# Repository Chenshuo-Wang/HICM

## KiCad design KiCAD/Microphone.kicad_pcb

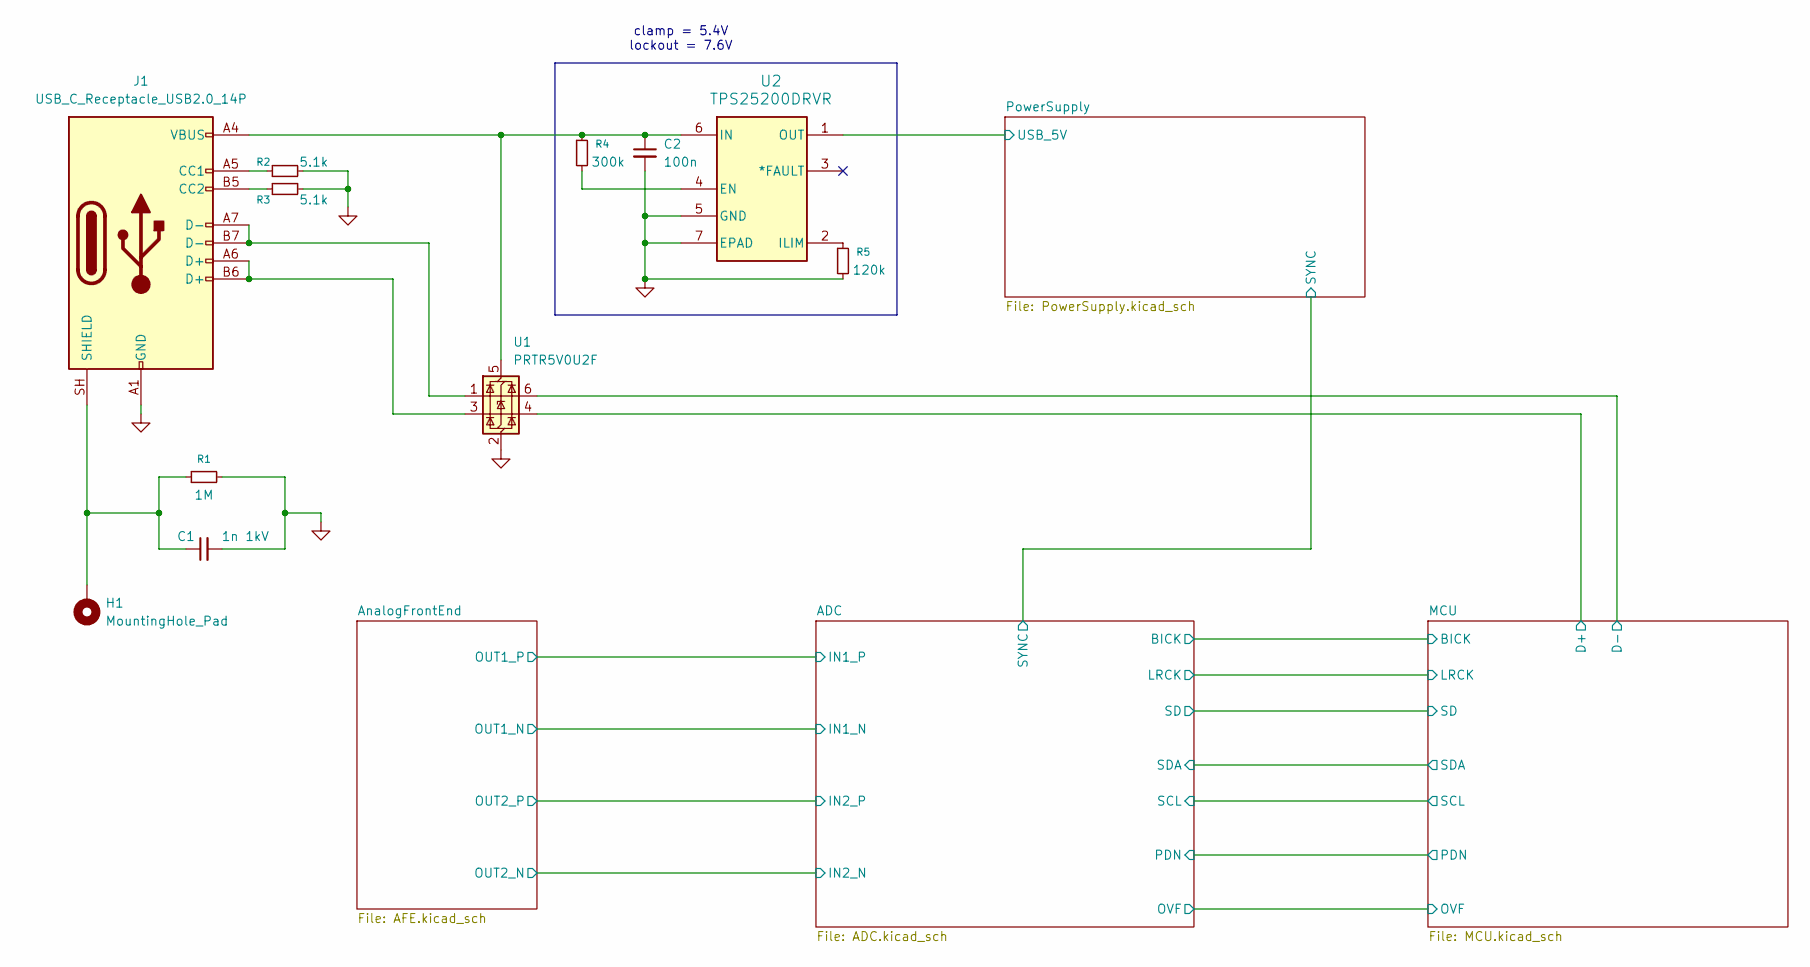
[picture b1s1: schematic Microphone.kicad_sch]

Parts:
C1: 1n 1kV; C_1206_3216Metric
C2: 100n; C_0402_1005Metric
H1: MountingHole_Pad; MountingHole_2.2mm_M2_Pad_Via
J1: USB_C_Receptacle_USB2.0_14P; USB_C_Receptacle_GCT_USB4110
R1: 1M; R_0805_2012Metric
R2, R3: 5.1k; R_0402_1005Metric
R4: 300k; R_0402_1005Metric
R5: 120k; R_0402_1005Metric
U1: PRTR5V0U2F; SOT-886
U2: TPS25200DRVR; DRV6_1X1P6_TEX

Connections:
/MCU/D+: U1.4 (I/O2); also elsewhere on the board
/MCU/D-: U1.6 (I/O1); also elsewhere on the board
/PowerSupply/USB_5V: U2.1 (OUT); also elsewhere on the board
GND: C1.2, C2.2, J1.A1 (GND), J1.A12 (GND), J1.B1 (GND), J1.B12 (GND), R1.2, R2.2, R3.1, R5.2, U1.2 (GND), U2.5 (GND), U2.7 (EPAD); also elsewhere on the board
unnamed: J1.A5 (CC1), R2.1
unnamed: J1.B5 (CC2), R3.2
unnamed: J1.A6 (D+), J1.B6 (D+), U1.3 (I/O2)
unnamed: J1.A7 (D-), J1.B7 (D-), U1.1 (I/O1)
unnamed: C1.1, H1.1 (1_1), J1.SH (SHIELD), R1.1
unnamed: C2.1, J1.A4 (VBUS), J1.A9 (VBUS), J1.B4 (VBUS), J1.B9 (VBUS), R4.1, U1.5 (VBUS), U2.6 (IN)
unnamed: R4.2, U2.4 (EN)
unnamed: R5.1, U2.2 (ILIM)

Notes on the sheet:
clamp = 5.4V lockout = 7.6V

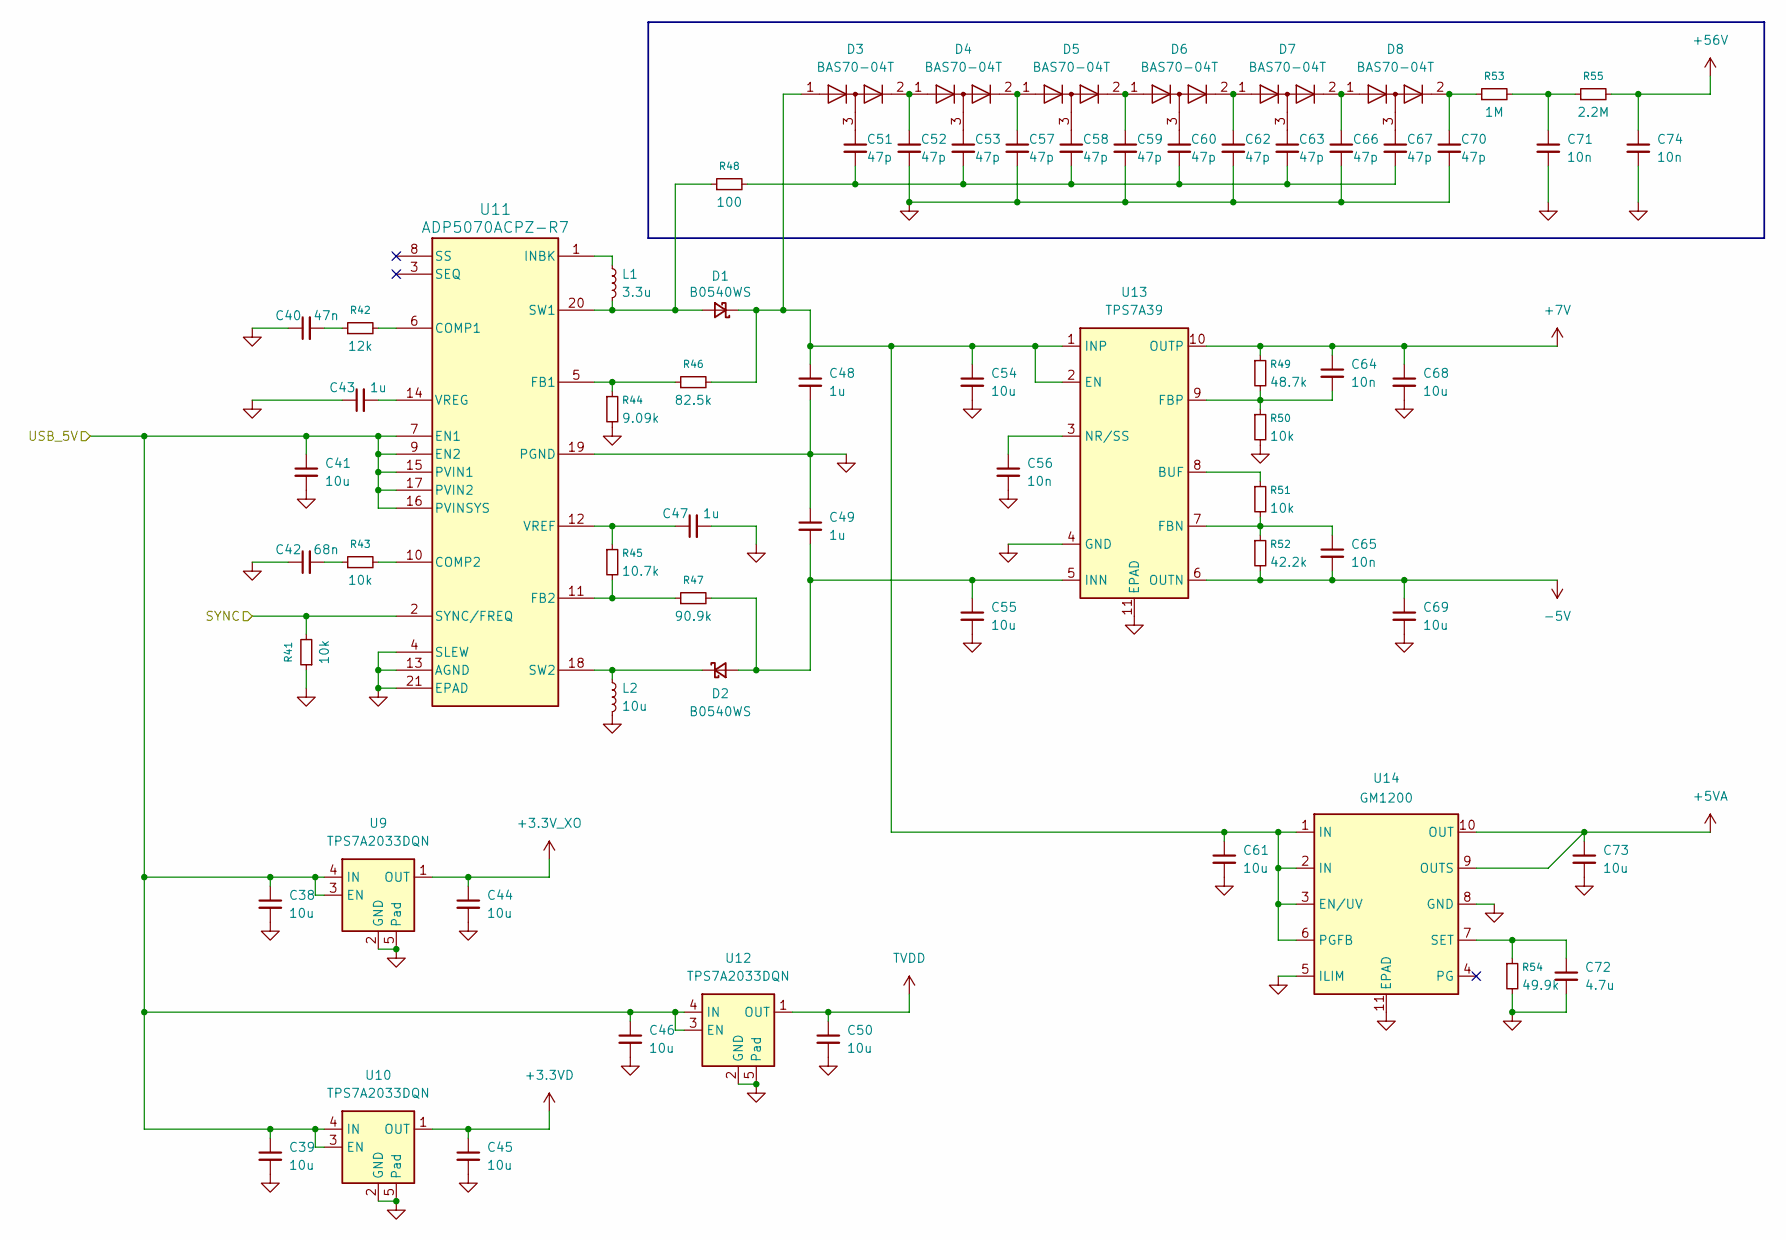
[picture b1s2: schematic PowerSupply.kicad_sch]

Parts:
C38, C39, C44, C45, C46, C50, C54, C55, C61, C68, C69, C73: 10u; C_0603_1608Metric
C40: 47n; C_0402_1005Metric
C41: 10u; C_0805_2012Metric
C42: 68n; C_0402_1005Metric
C43, C47: 1u; C_0402_1005Metric
C48, C49: 1u; C_0603_1608Metric
C51, C52, C53, C57, C58, C59, C60, C62, C63, C66, C67, C70: 47p; C_0603_1608Metric
C56, C64, C65: 10n; C_0402_1005Metric
C71, C74: 10n; C_0603_1608Metric
C72: 4.7u; C_0603_1608Metric
D1, D2: B0540WS; D_SOD-323
D3, D4, D5, D6, D7, D8: BAS70-04T; SOT-523
L1: 3.3u; IND_SPM4020_TDK
L2: 10u; IND_SPM4020_TDK
R41, R43, R50, R51: 10k; R_0402_1005Metric
R42: 12k; R_0402_1005Metric
R44: 9.09k; R_0402_1005Metric
R45: 10.7k; R_0402_1005Metric
R46: 82.5k; R_0402_1005Metric
R47: 90.9k; R_0402_1005Metric
R48: 100; R_0805_2012Metric
R49: 48.7k; R_0402_1005Metric
R52: 42.2k; R_0402_1005Metric
R53: 1M; R_0805_2012Metric
R54: 49.9k; R_0402_1005Metric
R55: 2.2M; R_0805_2012Metric
U9, U10, U12: TPS7A2033DQN; Texas_X2SON-4_1x1mm_P0.65mm
U11: ADP5070ACPZ-R7; QFN-20-1EP_4x4mm_P0.5mm_EP2.6x2.6mm_ThermalVias
U13: TPS7A39; Texas_S-PVSON-N10_ThermalVias
U14: GM1200; DFN-10-1EP_3x3mm_P0.5mm_EP1.65x2.38mm_ThermalVias

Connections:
+3.3VD: C45.1, U10.1 (OUT); also elsewhere on the board
+3.3V_XO: C44.1, U9.1 (OUT); also elsewhere on the board
+5VA: C73.1, U14.9 (OUTS), U14.10 (OUT); also elsewhere on the board
+7V: C64.1, C68.1, R49.1, U13.10 (OUTP); also elsewhere on the board
+56V: C74.1, R55.2; also elsewhere on the board
-5V: C65.2, C69.1, R52.2, U13.6 (OUTN); also elsewhere on the board
/ADC/SYNC: R41.2, U11.2 (SYNC/FREQ); also elsewhere on the board
/PowerSupply/USB_5V: C38.1, C39.1, C41.1, C46.1, U9.3 (EN), U9.4 (IN), U10.3 (EN), U10.4 (IN), U11.7 (EN1), U11.9 (EN2), U11.15 (PVIN1), U11.16 (PVINSYS), U11.17 (PVIN2), U12.3 (EN), U12.4 (IN); also elsewhere on the board
GND: C38.2, C39.2, C40.1, C41.2, C42.1, C43.1, C44.2, C45.2, C46.2, C47.2, C48.2, C49.1, C50.2, C52.2, C54.2, C55.2, C56.2, C57.2, C59.2, C61.2, C62.2, C66.2, C68.2, C69.2, C70.2, C71.2, C72.2, C73.2, C74.2, L2.2, R41.1, R44.2, R50.2, R54.2, U9.2 (GND), U9.5 (Pad), U10.2 (GND), U10.5 (Pad), U11.4 (SLEW), U11.13 (AGND), U11.19 (PGND), U11.21 (EPAD), U12.2 (GND), U12.5 (Pad), U13.4 (GND), U13.11 (EPAD), U14.5 (ILIM), U14.8 (GND), U14.11 (EPAD); also elsewhere on the board
unnamed: C40.2, R42.1
unnamed: C42.2, R43.1
unnamed: C51.1, D3.3 (K)
unnamed: C51.2, C53.2, C58.2, C60.2, C63.2, C67.2, R48.2
unnamed: C53.1, D4.3 (K)
unnamed: C58.1, D5.3 (K)
unnamed: C60.1, D6.3 (K)
unnamed: C63.1, D7.3 (K)
unnamed: C67.1, D8.3 (K)
unnamed: C71.1, R53.2, R55.1
unnamed: D1.2 (A), L1.2, R48.1, U11.20 (SW1)
unnamed: C48.1, C54.1, C61.1, D1.1 (K), D3.1 (K), R46.2, U13.1 (INP), U13.2 (EN), U14.1 (IN), U14.2 (IN), U14.3 (EN/UV), U14.6 (PGFB)
unnamed: C49.2, C55.1, D2.2 (A), R47.2, U13.5 (INN)
unnamed: D2.1 (K), L2.1, U11.18 (SW2)
unnamed: C52.1, D3.2 (A), D4.1 (K)
unnamed: C57.1, D4.2 (A), D5.1 (K)
unnamed: C59.1, D5.2 (A), D6.1 (K)
unnamed: C62.1, D6.2 (A), D7.1 (K)
unnamed: C66.1, D7.2 (A), D8.1 (K)
unnamed: C70.1, D8.2 (A), R53.1
unnamed: R42.2, U11.6 (COMP1)
unnamed: R43.2, U11.10 (COMP2)
unnamed: R44.1, R46.1, U11.5 (FB1)
unnamed: R45.2, R47.1, U11.11 (FB2)
unnamed: L1.1, U11.1 (INBK)
unnamed: C47.1, R45.1, U11.12 (VREF)
unnamed: C43.2, U11.14 (VREG)
unnamed: R51.1, U13.8 (BUF)
unnamed: C65.1, R51.2, R52.1, U13.7 (FBN)
unnamed: C64.2, R49.2, R50.1, U13.9 (FBP)
unnamed: C56.1, U13.3 (NR/SS)
unnamed: C72.1, R54.1, U14.7 (SET)
TVDD: C50.1, U12.1 (OUT); also elsewhere on the board

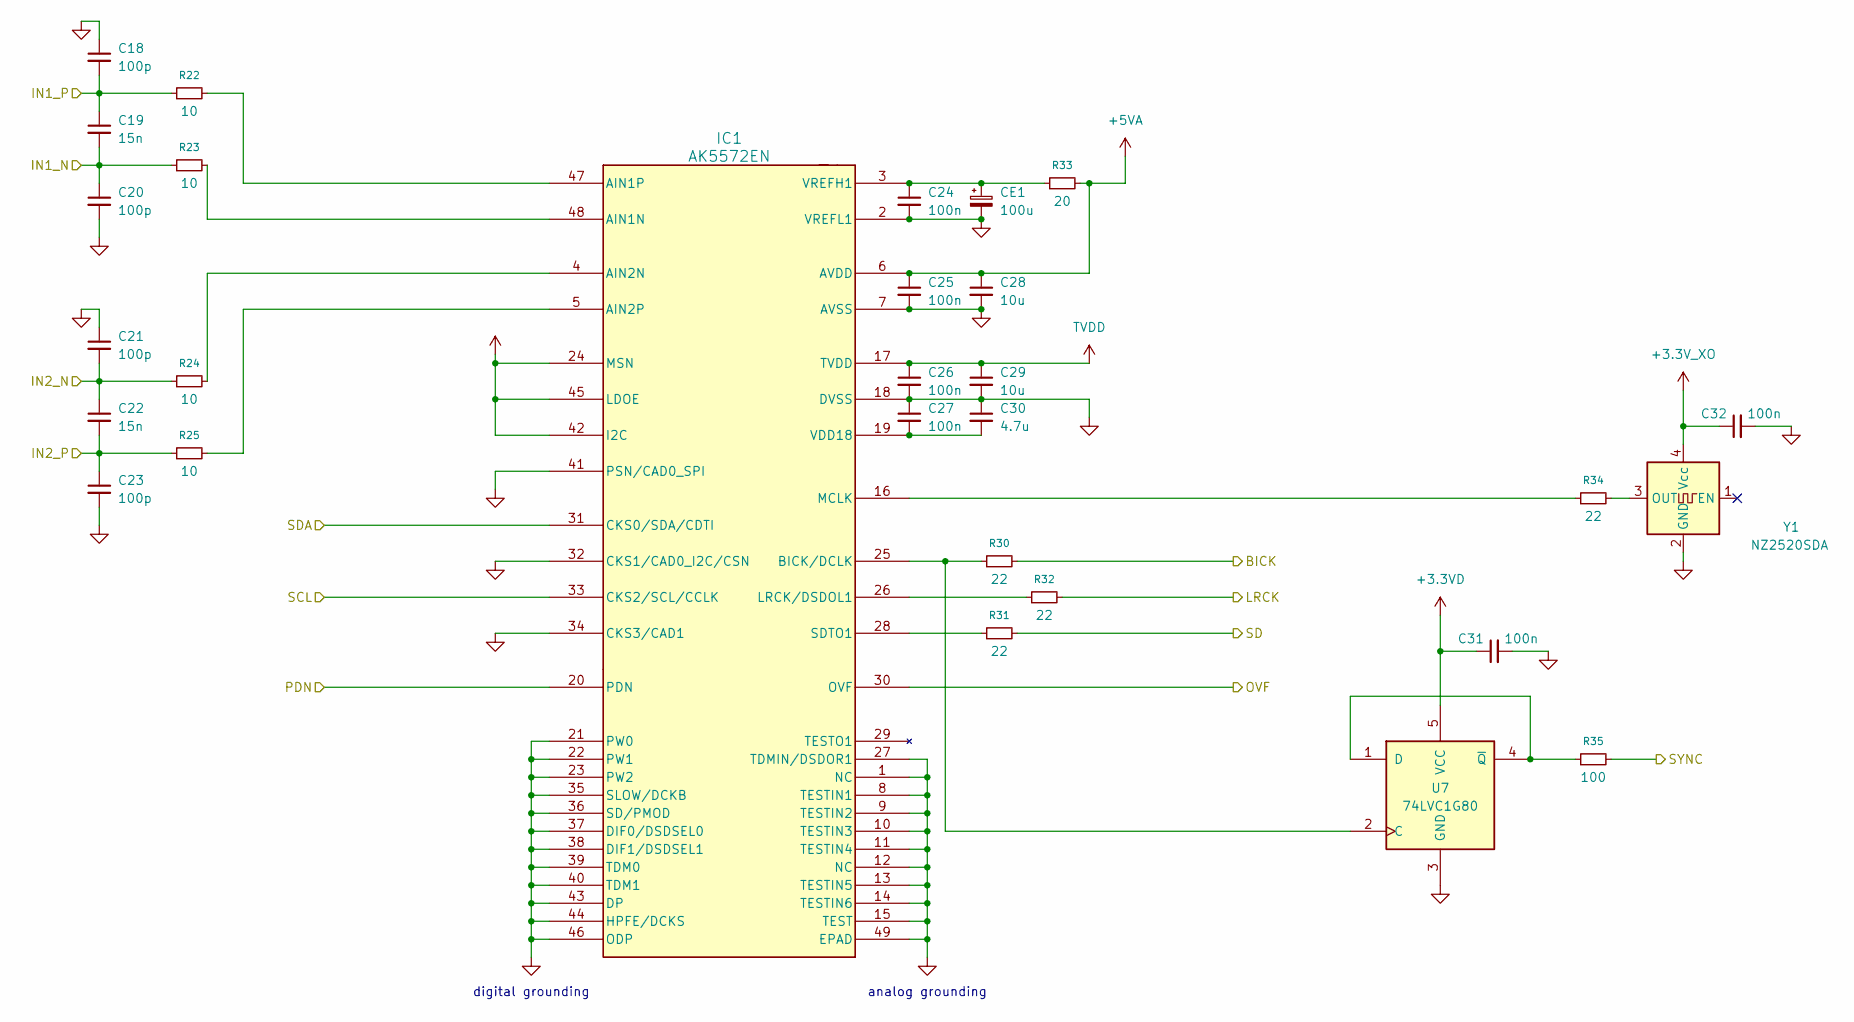
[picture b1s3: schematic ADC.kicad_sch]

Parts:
C18, C20, C21, C23: 100p; C_0402_1005Metric
C19, C22: 15n; C_0402_1005Metric
C24, C25, C26, C27, C31, C32: 100n; C_0402_1005Metric
C28, C29: 10u; C_0603_1608Metric
C30: 4.7u; C_0603_1608Metric
CE1: 100u; CP_EIA-3528-21_Kemet-B
IC1: AK5572EN; QFN-48-1EP_7x7mm_P0.5mm_EP5.1x5.1mm_ThermalVias
R22, R23, R24, R25: 10; R_0402_1005Metric
R30, R31, R32, R34: 22; R_0402_1005Metric
R33: 20; R_0805_2012Metric
R35: 100; R_0402_1005Metric
U7: 74LVC1G80; SOT-353_SC-70-5
Y1: NZ2520SDA; Oscillator_SMD_SeikoEpson_SG210-4Pin_2.5x2.0mm

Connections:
+3.3VD: C31.1, U7.5 (VCC); also elsewhere on the board
+3.3V_XO: C32.1, Y1.4 (Vcc); also elsewhere on the board
+5VA: C25.1, C28.1, IC1.6 (AVDD), R33.2; also elsewhere on the board
/ADC/BICK: R30.2; also elsewhere on the board
/ADC/IN1_N: C19.2, C20.1, R23.1; also elsewhere on the board
/ADC/IN1_P: C18.2, C19.1, R22.1; also elsewhere on the board
/ADC/IN2_N: C21.2, C22.1, R24.1; also elsewhere on the board
/ADC/IN2_P: C22.2, C23.1, R25.1; also elsewhere on the board
/ADC/LRCK: R32.2; also elsewhere on the board
/ADC/OVF: IC1.30 (OVF); also elsewhere on the board
/ADC/PDN: IC1.20 (PDN); also elsewhere on the board
/ADC/SCL: IC1.33 (CKS2/SCL/CCLK); also elsewhere on the board
/ADC/SD: R31.2; also elsewhere on the board
/ADC/SDA: IC1.31 (CKS0/SDA/CDTI); also elsewhere on the board
/ADC/SYNC: R35.2; also elsewhere on the board
GND: C18.1, C20.2, C21.1, C23.2, C24.2, C25.2, C26.2, C27.1, C28.2, C29.2, C30.1, C31.2, C32.2, CE1.2, IC1.1 (NC), IC1.2 (VREFL1), IC1.7 (AVSS), IC1.8 (TESTIN1), IC1.9 (TESTIN2), IC1.10 (TESTIN3), IC1.11 (TESTIN4), IC1.12 (NC), IC1.13 (TESTIN5), IC1.14 (TESTIN6), IC1.15 (TEST), IC1.18 (DVSS), IC1.21 (PW0), IC1.22 (PW1), IC1.23 (PW2), IC1.27 (TDMIN/DSDOR1), IC1.32 (CKS1/CAD0_I2C/CSN), IC1.34 (CKS3/CAD1), IC1.35 (SLOW/DCKB), IC1.36 (SD/PMOD), IC1.37 (DIF0/DSDSEL0), IC1.38 (DIF1/DSDSEL1), IC1.39 (TDM0), IC1.40 (TDM1), IC1.41 (PSN/CAD0_SPI), IC1.43 (DP), IC1.44 (HPFE/DCKS), IC1.46 (ODP), IC1.49 (EPAD), U7.3 (GND), Y1.2 (GND); also elsewhere on the board
unnamed: IC1.48 (AIN1N), R23.2
unnamed: IC1.47 (AIN1P), R22.2
unnamed: IC1.4 (AIN2N), R24.2
unnamed: IC1.5 (AIN2P), R25.2
unnamed: IC1.25 (BICK/DCLK), R30.1, U7.2 (C)
unnamed: IC1.26 (LRCK/DSDOL1), R32.1
unnamed: IC1.16 (MCLK), R34.1
unnamed: IC1.28 (SDTO1), R31.1
unnamed: C27.2, C30.2, IC1.19 (VDD18)
unnamed: C24.1, CE1.1, IC1.3 (VREFH1), R33.1
unnamed: R35.1, U7.1 (D), U7.4 (~Q)
unnamed: R34.2, Y1.3 (OUT)
TVDD: C26.1, C29.1, IC1.17 (TVDD), IC1.24 (MSN), IC1.42 (I2C), IC1.45 (LDOE); also elsewhere on the board

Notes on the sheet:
analog grounding
digital grounding

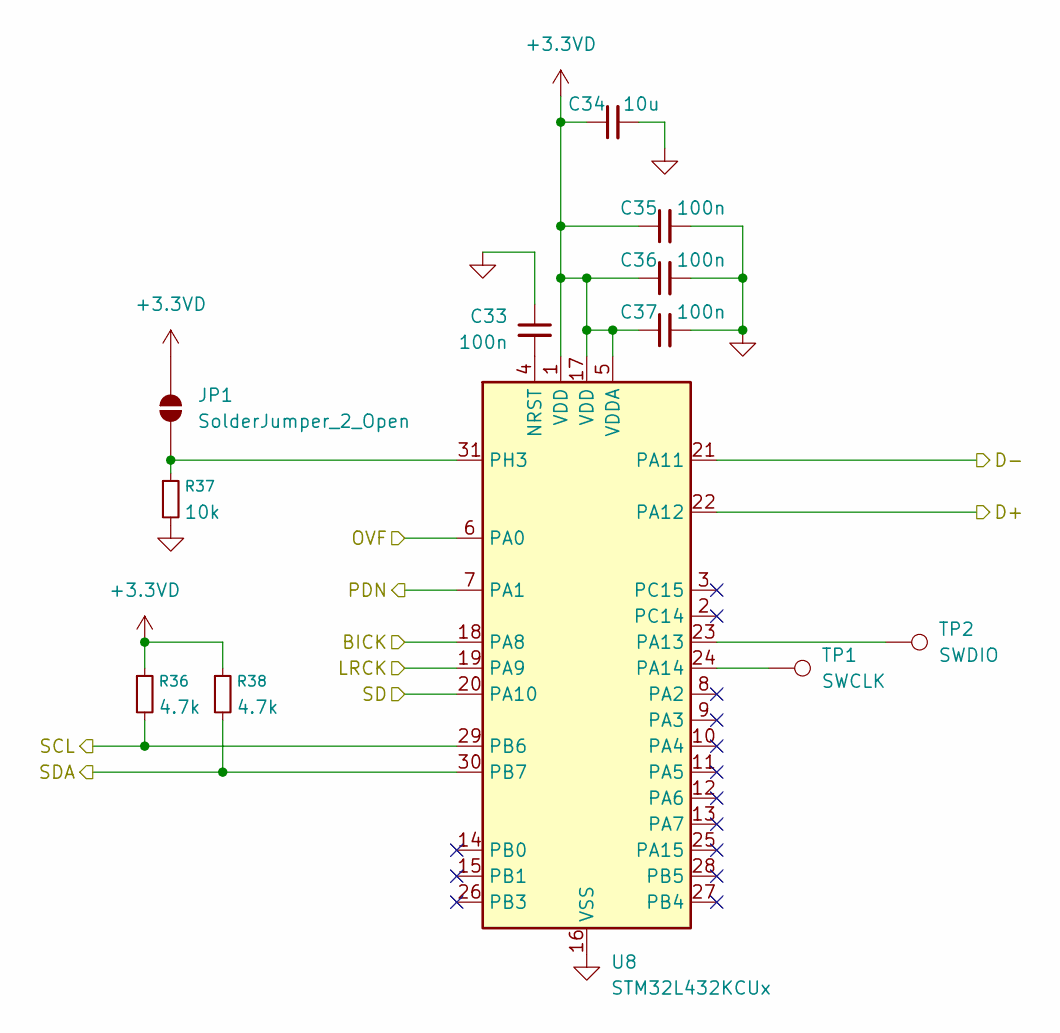
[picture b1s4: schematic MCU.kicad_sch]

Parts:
C33, C35, C36, C37: 100n; C_0402_1005Metric
C34: 10u; C_0603_1608Metric
JP1: SolderJumper_2_Open; SolderJumper-2_P1.3mm_Open_RoundedPad1.0x1.5mm
R36, R38: 4.7k; R_0402_1005Metric
R37: 10k; R_0402_1005Metric
TP1: SWCLK; TestPoint_Pad_D1.0mm
TP2: SWDIO; TestPoint_Pad_D1.0mm
U8: STM32L432KCUx; QFN-32-1EP_5x5mm_P0.5mm_EP3.45x3.45mm_ThermalVias

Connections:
+3.3VD: C34.1, C35.1, C36.1, C37.1, JP1.2 (B), R36.1, R38.1, U8.1 (VDD), U8.5 (VDDA), U8.17 (VDD); also elsewhere on the board
/ADC/BICK: U8.18 (PA8); also elsewhere on the board
/ADC/LRCK: U8.19 (PA9); also elsewhere on the board
/ADC/OVF: U8.6 (PA0); also elsewhere on the board
/ADC/PDN: U8.7 (PA1); also elsewhere on the board
/ADC/SCL: R36.2, U8.29 (PB6); also elsewhere on the board
/ADC/SD: U8.20 (PA10); also elsewhere on the board
/ADC/SDA: R38.2, U8.30 (PB7); also elsewhere on the board
/MCU/D+: U8.22 (PA12); also elsewhere on the board
/MCU/D-: U8.21 (PA11); also elsewhere on the board
GND: C33.1, C34.2, C35.2, C36.2, C37.2, R37.2, U8.16 (VSS), U8.32 (VSS), U8.33 (VSS); also elsewhere on the board
unnamed: JP1.1 (A), R37.1, U8.31 (PH3)
unnamed: C33.2, U8.4 (NRST)
unnamed: TP2.1 (1_1), U8.23 (PA13)
unnamed: TP1.1 (1_1), U8.24 (PA14)

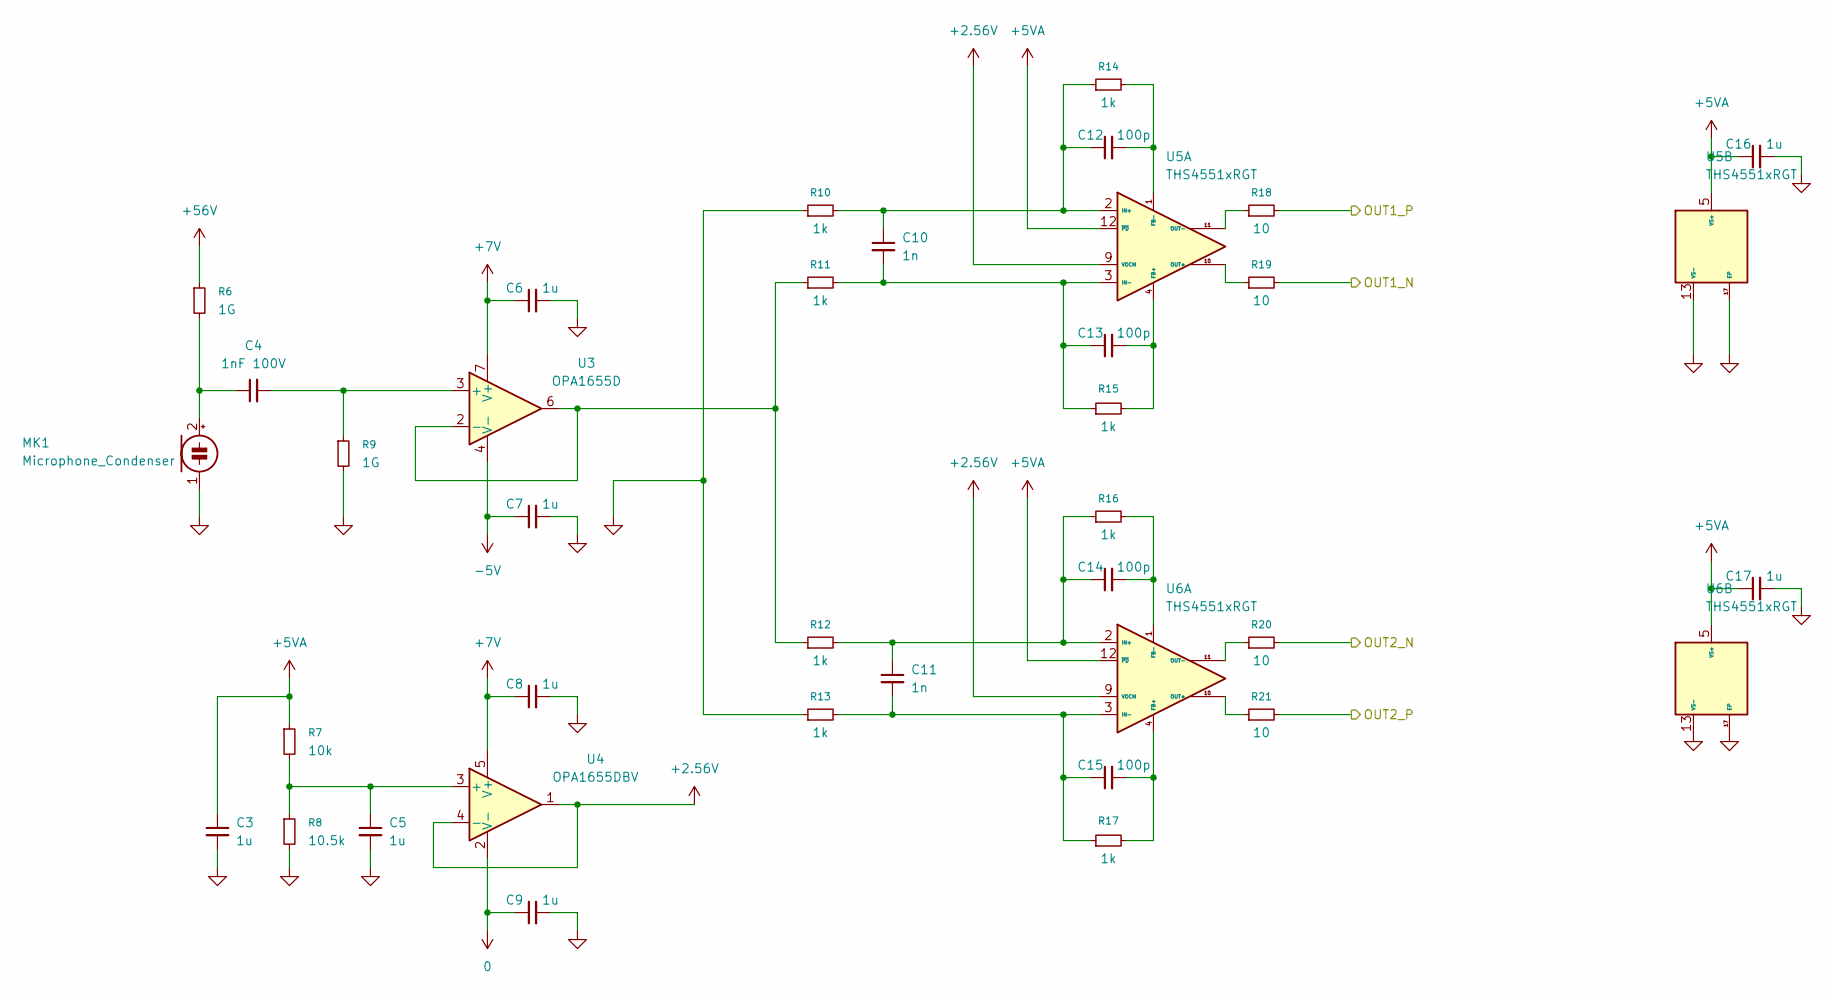
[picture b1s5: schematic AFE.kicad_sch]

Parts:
C3, C5, C6, C7, C8, C9, C16, C17: 1u; C_0402_1005Metric
C4: 1nF 100V; C_0805_2012Metric
C10, C11: 1n; C_0402_1005Metric
C12, C13, C14, C15: 100p; C_0402_1005Metric
MK1: Microphone_Condenser; SolderWire-0.5sqmm_1x02_P4.6mm_D0.9mm_OD2.1mm
R6, R9: 1G; R_0805_2012Metric
R7: 10k; R_0402_1005Metric
R8: 10.5k; R_0402_1005Metric
R10, R11, R12, R13, R14, R15, R16, R17: 1k; R_0402_1005Metric
R18, R19, R20, R21: 10; R_0402_1005Metric
U3: OPA1655D; SOIC-8_3.9x4.9mm_P1.27mm
U4: OPA1655DBV; SOT-23-5
U5, U6: THS4551xRGT; VQFN-16-1EP_3x3mm_P0.5mm_EP1.68x1.68mm

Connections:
0: C9.1, U4.2 (V-)
+2.56V: U4.1, U4.4 (-), U5.9 (VOCM), U6.9 (VOCM)
+5VA: C3.1, C16.1, C17.1, R7.1, U5.5 (VS+), U5.6 (VS+), U5.7 (VS+), U5.8 (VS+), U5.12 (~PD), U6.5 (VS+), U6.6 (VS+), U6.7 (VS+), U6.8 (VS+), U6.12 (~PD); also elsewhere on the board
+7V: C6.1, C8.1, U3.7 (V+), U4.5 (V+); also elsewhere on the board
+56V: R6.1; also elsewhere on the board
-5V: C7.1, U3.4 (V-); also elsewhere on the board
/ADC/IN1_N: R19.2; also elsewhere on the board
/ADC/IN1_P: R18.2; also elsewhere on the board
/ADC/IN2_N: R20.2; also elsewhere on the board
/ADC/IN2_P: R21.2; also elsewhere on the board
GND: C3.2, C5.2, C6.2, C7.2, C8.2, C9.2, C16.2, C17.2, MK1.1 (-), R8.2, R9.2, R10.1, R13.1, U5.13 (VS-), U5.14 (VS-), U5.15 (VS-), U5.16 (VS-), U5.17 (EP), U6.13 (VS-), U6.14 (VS-), U6.15 (VS-), U6.16 (VS-), U6.17 (EP); also elsewhere on the board
unnamed: C4.1, MK1.2 (+), R6.2
unnamed: C4.2, R9.1, U3.3 (+)
unnamed: R11.1, R12.1, U3.2 (-), U3.6
unnamed: C5.1, R7.2, R8.1, U4.3 (+)
unnamed: C13.2, R15.2, U5.4 (FB+)
unnamed: C12.2, R14.2, U5.1 (FB-)
unnamed: C10.1, C12.1, R10.2, R14.1, U5.2 (IN+)
unnamed: C10.2, C13.1, R11.2, R15.1, U5.3 (IN-)
unnamed: R19.1, U5.10 (OUT+)
unnamed: R18.1, U5.11 (OUT-)
unnamed: C15.2, R17.2, U6.4 (FB+)
unnamed: C14.2, R16.2, U6.1 (FB-)
unnamed: C11.1, C14.1, R12.2, R16.1, U6.2 (IN+)
unnamed: C11.2, C15.1, R13.2, R17.1, U6.3 (IN-)
unnamed: R21.1, U6.10 (OUT+)
unnamed: R20.1, U6.11 (OUT-)

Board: 2 copper layers, 156 parts (40 on the bottom side), 97 nets, no tracks yet.
